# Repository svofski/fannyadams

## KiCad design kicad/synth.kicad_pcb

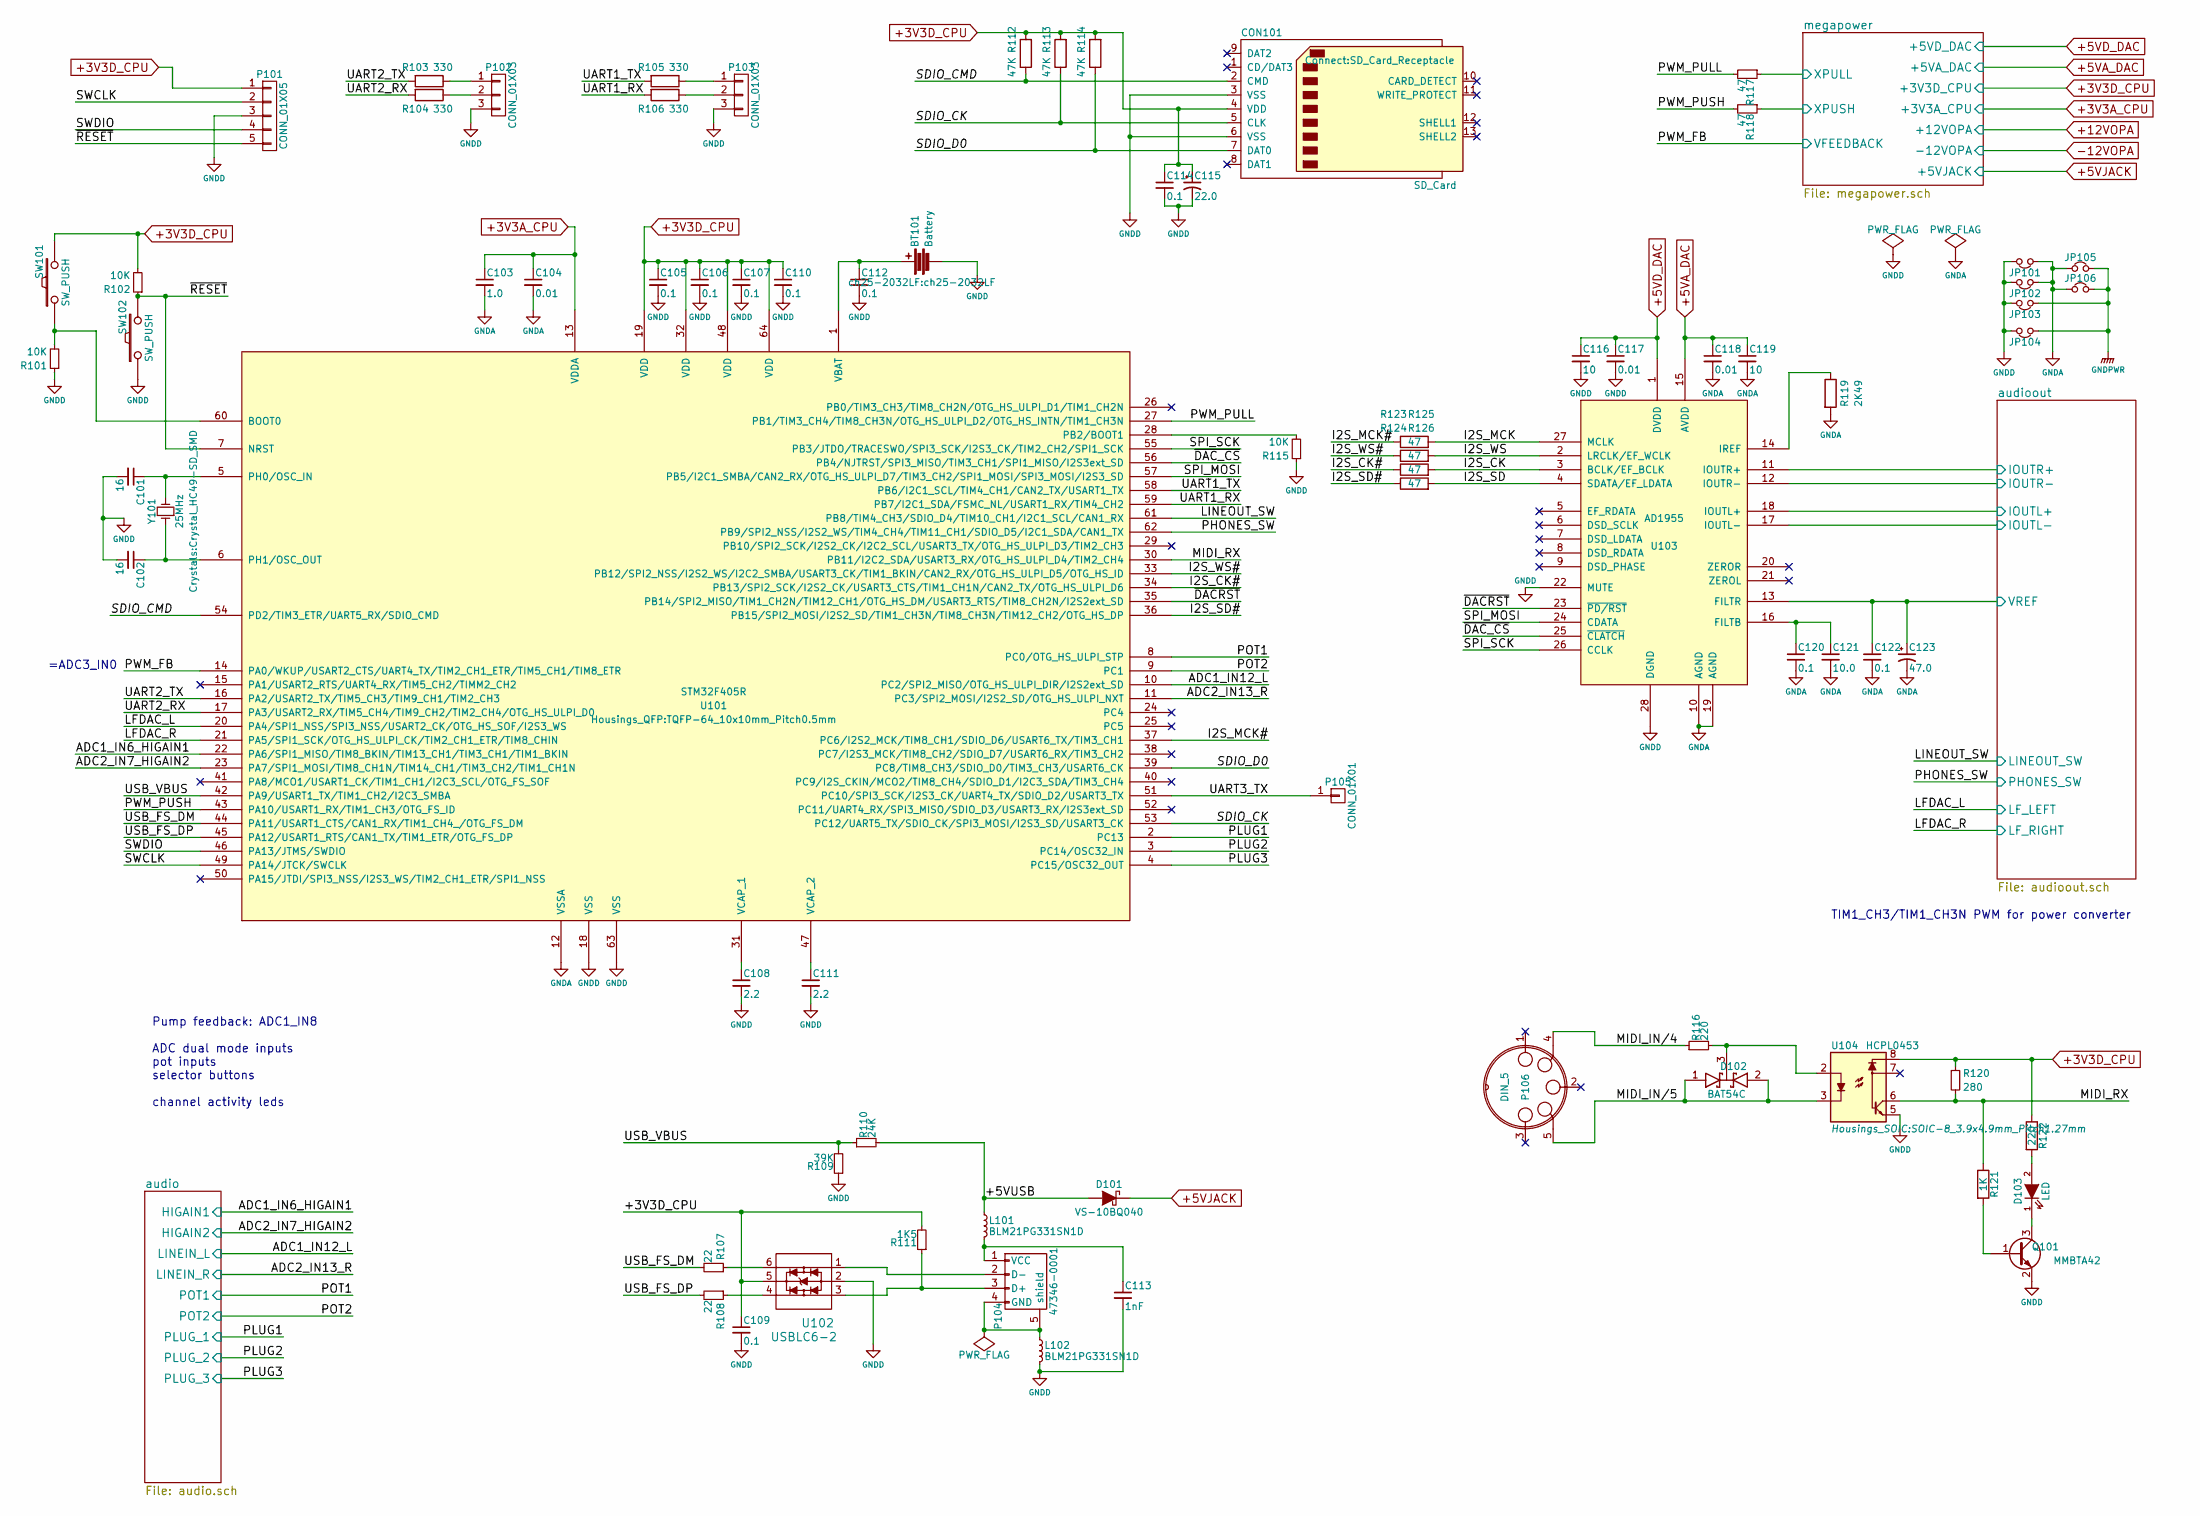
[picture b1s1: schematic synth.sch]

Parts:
BT101: Battery; ch25-2032LF
C101, C102: 16; C_0805
C103: 1.0; C_0805
C104, C117, C118: 0.01; C_0805
C105, C106, C107, C110, C112, C114, C120, C122: 0.1; C_0603
C108, C111: 2.2; C_0805
C109: 0.1; C_0805
C113: 1nF; C_0805
C115: 22.0; TantalC_SizeD_EIA-7343_Reflow
C116, C119: 10; C_0805
C121: 10.0; C_0805
C123: 47.0; c_elec_5x5.3
CON101: SD_Card; SD_Card_Receptacle
D101: VS-10BQ040; SMB_Standard
D102: BAT54C; SOT-23
D103: LED; LED-0805
JP101, JP102, JP103, JP104, JP105, JP106: Jumper_NC_Small; R_0603
L101, L102: BLM21PG331SN1D; R_0805
P101: CONN_01X05; Pin_Header_Straight_1x05
P102, P103: CONN_01X03; Pin_Header_Straight_1x03
P104: 47346-0001; USB_Micro-B
P105: CONN_01X01; 1Pin
P106: DIN_5; din-5
Q101: MMBTA42; SOT-23
R101, R102, R115: 10K; R_0805
R103, R104, R105, R106: 330; R_0805
R107, R108: 22; R_0805
R109: 39K; R_0805
R110: 24K; R_0805
R111: 1K5; R_0805
R112, R113, R114: 47K; R_0805
R116, R122: 220; R_0805
R117, R118, R123, R124, R125, R126: 47; R_0402
R119: 2K49; R_0805
R120: 280; R_0805
R121: 1K; R_0805
SW101, SW102: SW_PUSH; SW_PUSH_SMALL
U101: STM32F405R; TQFP-64_10x10mm_Pitch0.5mm
U102: USBLC6-2; SOT-23-6
U103: AD1955; SSOP-28_5.3x10.2mm_Pitch0.65mm
U104: HCPL0453; SOIC-8_3.9x4.9mm_Pitch1.27mm
Y101: 25MHz; Crystal_HC49-SD_SMD

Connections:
+3V3D_CPU: C105.1, C106.1, C107.1, C109.1, C110.1, C114.1, C115.1, CON101.4 (VDD), P101.1, R102.2, R111.2, R112.2, R113.2, R114.2, R120.1, R122.1, SW101.2, U101.19 (VDD), U101.32 (VDD), U101.48 (VDD), U101.64 (VDD), U102.5, U104.8; also elsewhere on the board
+5VA_DAC: C118.1, C119.1, U103.15 (AVDD); also elsewhere on the board
+5VD_DAC: C116.1, C117.1, U103.1 (DVDD); also elsewhere on the board
+5VJACK: D101.1 (K); also elsewhere on the board
/+5VUSB: D101.2 (A), L101.1, R110.2
/I2S_CK: R125.2, U103.3 (BCLK/EF_BCLK)
/I2S_CK#: R125.1, U101.34 (PB13/SPI2_SCK/I2S2_CK/USART3_CTS/TIM1_C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)
/I2S_MCK: R123.2, U103.27 (MCLK)
/I2S_MCK#: R123.1, U101.37 (PC6/I2S2_MCK/TIM8_CH1/SDIO_D6/USART6_TX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)
/I2S_SD: R126.2, U103.4 (SDATA/EF_LDATA)
/I2S_SD#: R126.1, U101.36 (PB15/SPI2_MOSI/I2S2_SD/TIM1_CH3N/TIM8_C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)
/I2S_WS: R124.2, U103.2 (LRCLK/EF_WCLK)
/I2S_WS#: R124.1, U101.33 (PB12/SPI2_NSS/I2S2_WS/I2C2_SMBA/USART3_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)
/MIDI_IN/4: P106.4, R116.1
/MIDI_IN/5: D102.1 (A), D102.2 (A), P106.5, U104.3
/MIDI_RX: R120.2, R121.1, U101.30 (PB11/I2C2_SDA/USART3_RX/OTG_HS_ULPI_D4/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), U104.6
/PWM_PULL: R117.2, U101.27 (PB1/TIM3_CH4/TIM8_CH3N/OTG_HS_ULPI_D2/O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)
/PWM_PUSH: R118.2, U101.43 (PA10/USART1_RX/TIM1_CH3/OTG_FS_ID)
/SDIO_CK: CON101.5 (CLK), R113.1, U101.53 (PC12/UART5_TX/SDIO_CK/SPI3_MOSI/I2S3_SD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)
/SDIO_CMD: CON101.2 (CMD), R112.1, U101.54 (PD2/TIM3_ETR/UART5_RX/SDIO_CMD)
/SDIO_D0: CON101.7 (DAT0), R114.1, U101.39 (PC8/TIM8_CH3/SDIO_D0/TIM3_CH3/USART6_CK)
/SPI_MOSI: U101.57 (PB5/I2C1_SMBA/CAN2_RX/OTG_HS_ULPI_D7/TI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), U103.24 (CDATA)
/SPI_SCK: U101.55 (PB3/JTDO/TRACESWO/SPI3_SCK/I2S3_CK/TIM2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), U103.26 (CCLK)
/SWCLK: P101.2, U101.49 (PA14/JTCK/SWCLK)
/SWDIO: P101.4, U101.46 (PA13/JTMS/SWDIO)
/UART1_RX: R106.2, U101.59 (PB7/I2C1_SDA/FSMC_NL/USART1_RX/TIM4_CH2)
/UART1_TX: R105.2, U101.58 (PB6/I2C1_SCL/TIM4_CH1/CAN2_TX/USART1_TX)
/UART2_RX: R104.2, U101.17 (PA3/USART2_RX/TIM5_CH4/TIM9_CH2/TIM2_CH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)
/UART2_TX: R103.2, U101.16 (PA2/USART2_TX/TIM5_CH3/TIM9_CH1/TIM2_CH3)
/UART3_TX: P105.1, U101.51 (PC10/SPI3_SCK/I2S3_CK/UART4_TX/SDIO_D2/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)
/USB_FS_DM: R107.2, U101.44 (PA11/USART1_CTS/CAN1_RX/TIM1_CH4_/OTG_F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)
/USB_FS_DP: R108.2, U101.45 (PA12/USART1_RTS/CAN1_TX/TIM1_ETR/OTG_FS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)
/USB_VBUS: R109.2, R110.1, U101.42 (PA9/USART1_TX/TIM1_CH2/I2C3_SMBA)
/audio/HIGAIN1: U101.22 (PA6/SPI1_MISO/TIM8_BKIN/TIM13_CH1/TIM3_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); also elsewhere on the board
/audio/HIGAIN2: U101.23 (PA7/SPI1_MOSI/TIM8_CH1N/TIM14_CH1/TIM3_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); also elsewhere on the board
/audio/LINEIN_L: U101.10 (PC2/SPI2_MISO/OTG_HS_ULPI_DIR/I2S2ext_SD); also elsewhere on the board
/audio/LINEIN_R: U101.11 (PC3/SPI2_MOSI/I2S2_SD/OTG_HS_ULPI_NXT); also elsewhere on the board
/audio/PLUG_1: U101.2 (PC13); also elsewhere on the board
/audio/PLUG_2: U101.3 (PC14/OSC32_IN); also elsewhere on the board
/audio/PLUG_3: U101.4 (PC15/OSC32_OUT); also elsewhere on the board
/audio/POT1: U101.8 (PC0/OTG_HS_ULPI_STP); also elsewhere on the board
/audio/POT2: U101.9 (PC1); also elsewhere on the board
/audioout/IOUTL+: U103.18 (IOUTL+); also elsewhere on the board
/audioout/IOUTL-: U103.17 (IOUTL-); also elsewhere on the board
/audioout/IOUTR+: U103.11 (IOUTR+); also elsewhere on the board
/audioout/IOUTR-: U103.12 (IOUTR-); also elsewhere on the board
/audioout/LF_LEFT: U101.20 (PA4/SPI1_NSS/SPI3_NSS/USART2_CK/OTG_HS_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); also elsewhere on the board
/audioout/LF_RIGHT: U101.21 (PA5/SPI1_SCK/OTG_HS_ULPI_CK/TIM2_CH1_ET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); also elsewhere on the board
/audioout/LINEOUT_SW: U101.61 (PB8/TIM4_CH3/SDIO_D4/TIM10_CH1/I2C1_SCL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); also elsewhere on the board
/audioout/PHONES_SW: U101.62 (PB9/SPI2_NSS/I2S2_WS/TIM4_CH4/TIM11_CH1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); also elsewhere on the board
/audioout/VREF: C122.1, C123.1, U103.13 (FILTR); also elsewhere on the board
/megapower/VFEEDBACK: U101.14 (PA0/WKUP/USART2_CTS/UART4_TX/TIM2_CH1_E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); also elsewhere on the board
/megapower/XPULL: R117.1; also elsewhere on the board
/megapower/XPUSH: R118.1; also elsewhere on the board
/~DACRST: U101.35 (PB14/SPI2_MISO/TIM1_CH2N/TIM12_CH1/OTG_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), U103.23 (~PD/RST)
/~DAC_CS: U101.56 (PB4/NJTRST/SPI3_MISO/TIM3_CH1/SPI1_MISO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), U103.25 (~CLATCH)
/~RESET: P101.5, R102.1, SW102.2, U101.7 (NRST)
GNDA: C103.2, C104.2, C118.2, C119.2, C120.2, C121.2, C122.2, C123.2, JP101.1, JP102.1, JP105.1, JP106.1, R119.2, U101.12 (VSSA), U103.10 (AGND), U103.19 (AGND); also elsewhere on the board
GNDD: BT101.2, C101.2, C102.2, C105.2, C106.2, C107.2, C108.2, C109.2, C110.2, C111.2, C112.2, C113.2, C114.2, C115.2, C116.2, C117.2, CON101.3 (VSS), CON101.6 (VSS), JP101.2, JP102.2, JP103.2, JP104.2, L102.2, P101.3, P102.3, P103.3, Q101.2 (E), R101.1, R109.1, R115.1, SW102.1, U101.18 (VSS), U101.63 (VSS), U102.2, U103.22 (MUTE), U103.28 (DGND), U104.5; also elsewhere on the board
GNDPWR: JP103.1, JP104.1, JP105.2, JP106.2; also elsewhere on the board
unnamed: BT101.1, C112.1, U101.1 (VBAT)
unnamed: C101.1, U101.5 (PH0/OSC_IN), Y101.2
unnamed: C102.1, U101.6 (PH1/OSC_OUT), Y101.1
unnamed: C108.1, U101.31 (VCAP_1)
unnamed: C111.1, U101.47 (VCAP_2)
unnamed: C113.1, L101.2, P104.1 (VCC)
unnamed: C120.1, C121.1, U103.16 (FILTB)
unnamed: D102.3 (K), R116.2, U104.2
unnamed: D103.1 (K), Q101.3 (C)
unnamed: D103.2 (A), R122.2
unnamed: L102.1, P104.4 (GND), P104.5 (shield)
unnamed: P102.1, R103.1
unnamed: P102.2, R104.1
unnamed: P103.1, R105.1
unnamed: P103.2, R106.1
unnamed: P104.2 (D-), U102.1
unnamed: P104.3 (D+), R111.1, U102.3
unnamed: Q101.1 (B), R121.2
unnamed: R101.2, SW101.1, U101.60 (BOOT0)
unnamed: R107.1, U102.6
unnamed: R108.1, U102.4
unnamed: R115.2, U101.28 (PB2/BOOT1)
unnamed: R119.1, U103.14 (IREF)

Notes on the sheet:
TIM1_CH3/TIM1_CH3N PWM for power converter
Pump feedback: ADC1_IN8 ADC dual mode inputs pot inputs selector buttons channel activity leds
=ADC3_IN0

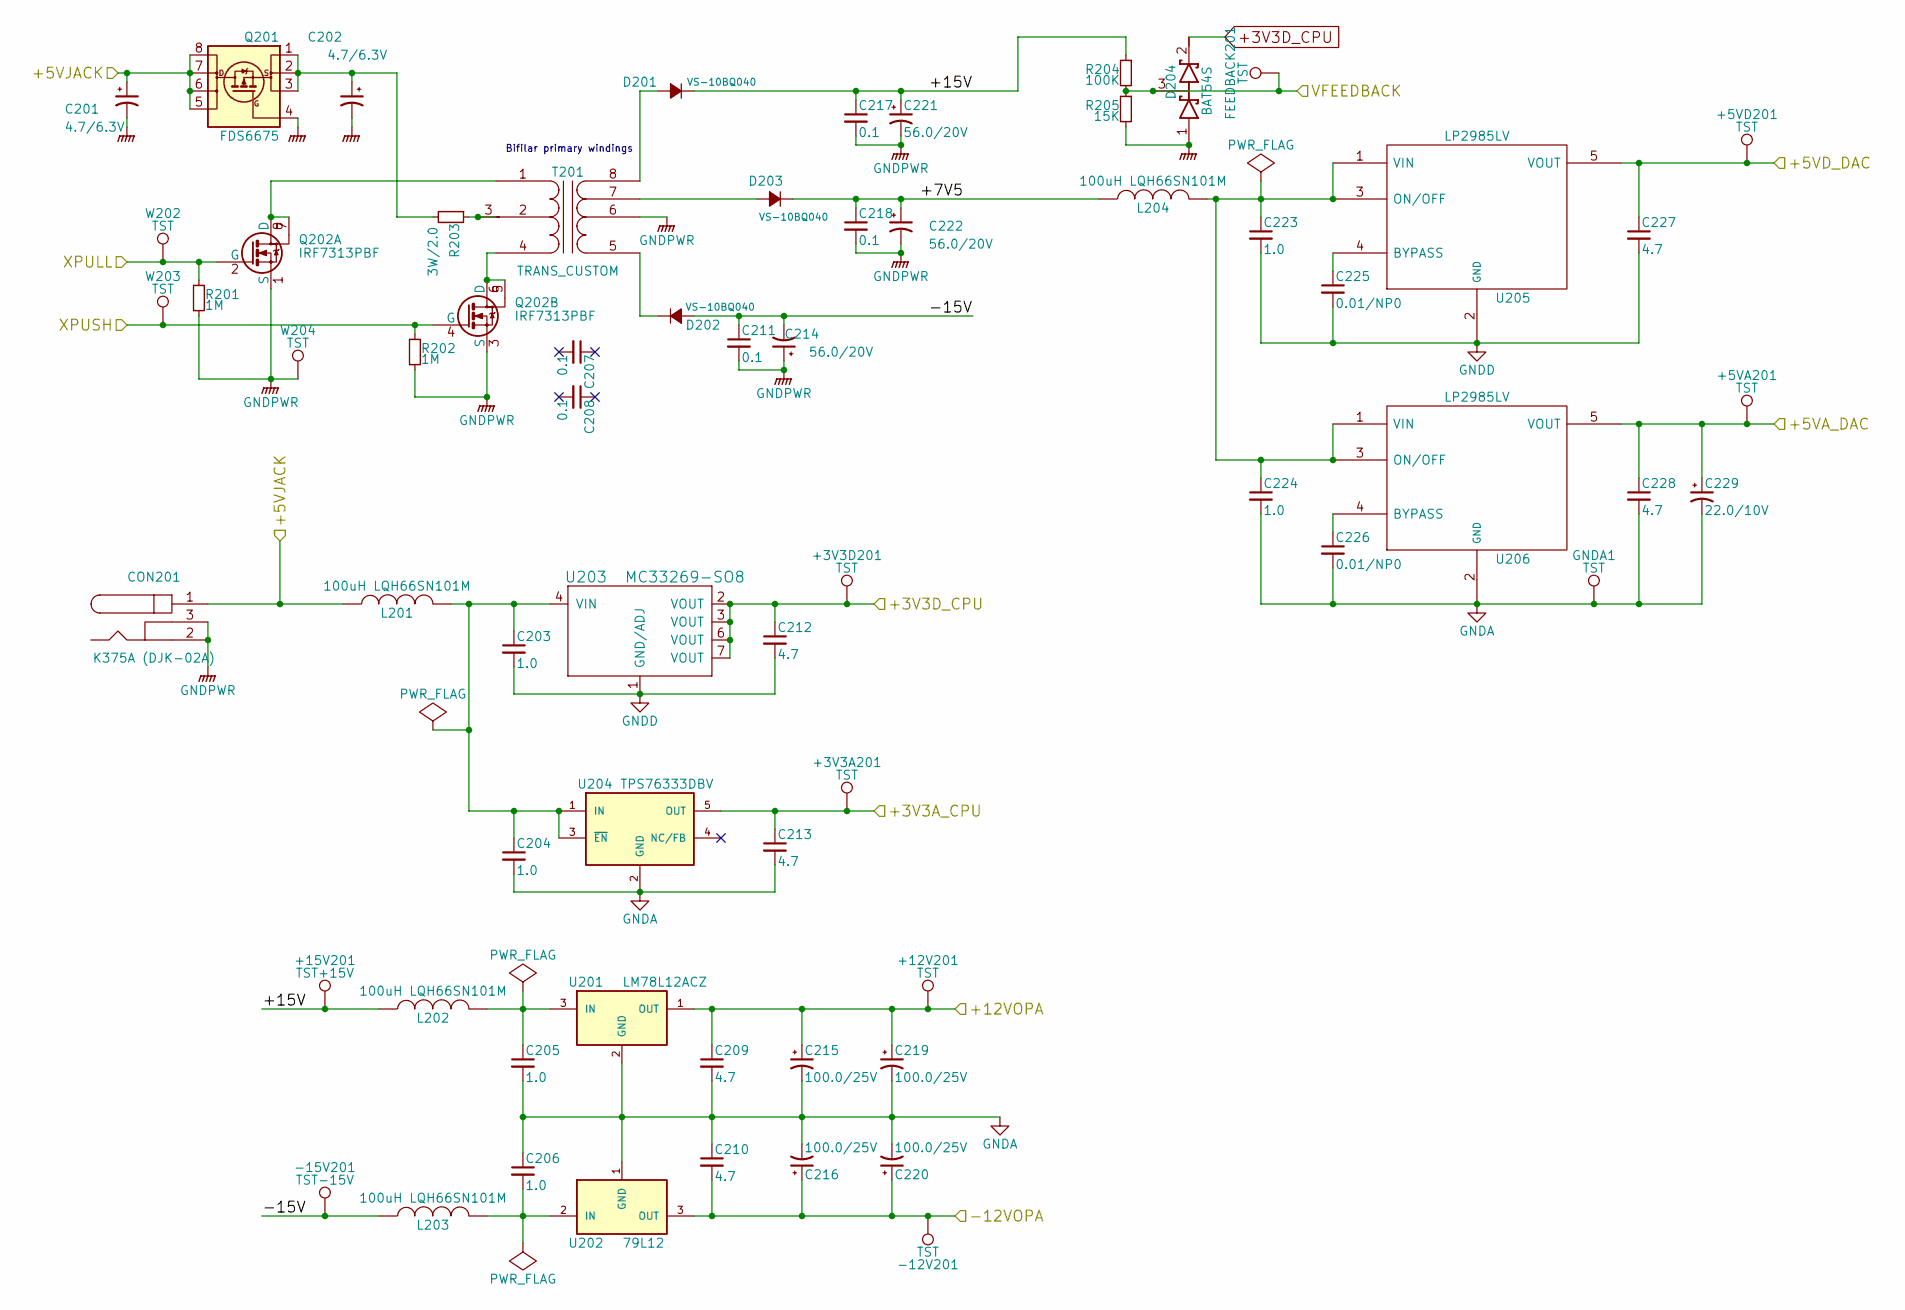
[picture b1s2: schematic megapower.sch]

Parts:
+3V3A201, +3V3D201, +5VA201, +5VD201, +12V201: TST; PINTST
+15V201: TST+15V; PINTST
-12V201: TST; PINTST
-15V201: TST-15V; PINTST
C201, C202: 4.7/6.3V; c_elec_5x5.3
C203, C204, C205, C206, C223, C224: 1.0; C_0805
C207, C208, C211: 0.1; C_0805
C209, C210, C212, C213, C227, C228: 4.7; C_0805
C214, C221, C222: 56.0/20V; C_Radial_D6.3_L11.2_P2.5
C215, C216, C219, C220: 100.0/25V; c_elec_6.3x7.7
C217, C218: 0.1; C_0603
C225, C226: 0.01/NP0; C_0805
C229: 22.0/10V; TantalC_SizeC_EIA-6032_Reflow
CON201: K375A (DJK-02A); BARREL_JACK
D201, D202, D203: VS-10BQ040; SMB_Standard
D204: BAT54S; SOT-23
FEEDBACK201: TST; PINTST
GNDA1: TST; PINTST
L201, L202, L203, L204: 100uH LQH66SN101M; Choke_SMD_6.3x6.3_H3
Q201: FDS6675; SOIC-8_3.9x4.9mm_Pitch1.27mm
Q202: IRF7313PBF; SO-8
R201, R202: 1M; R_0805
R203: 3W/2.0; R_0805
R204: 100K; R_0805
R205: 15K; R_0805
T201: TRANS_CUSTOM; Coilcraft-Q4434-B_Rhombus-T1311
U201: LM78L12ACZ; TO-92_Inline_Wide
U202: 79L12; TO-92_Inline_Wide
U203: MC33269-SO8; SOIC-8_3.9x4.9mm_Pitch1.27mm
U204: TPS76333DBV; SOT-23-5
U205, U206: LP2985LV; SOT-23-5
W202, W203, W204: TST; PINTST

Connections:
+3V3D_CPU: +3V3D201.1, C212.1, D204.2 (K), U203.2 (VOUT), U203.3 (VOUT), U203.6 (VOUT), U203.7 (VOUT); also elsewhere on the board
+5VA_DAC: +5VA201.1, C228.1, C229.1, U206.5 (VOUT); also elsewhere on the board
+5VD_DAC: +5VD201.1, C227.1, U205.5 (VOUT); also elsewhere on the board
+5VJACK: C201.1, CON201.1, L201.1, Q201.5 (D), Q201.6 (D), Q201.7 (D), Q201.8 (D); also elsewhere on the board
+12VOPA: +12V201.1, C209.1, C215.1, C219.1, U201.1 (OUT); also elsewhere on the board
-12VOPA: -12V201.1, C210.2, C216.1, C220.1, U202.3 (OUT); also elsewhere on the board
/megapower/+7V5: C218.1, C222.1, D203.1 (K), L204.1
/megapower/+15V: +15V201.1, C217.1, C221.1, D201.1 (K), L202.1, R204.1
/megapower/-15V: -15V201.1, C211.1, C214.2, D202.2 (A), L203.1
/megapower/VFEEDBACK: D204.3 (common), FEEDBACK201.1, R204.2, R205.1; also elsewhere on the board
/megapower/XPULL: Q202.2 (G), R201.1, W202.1; also elsewhere on the board
/megapower/XPUSH: Q202.4 (G), R202.1, W203.1; also elsewhere on the board
GNDA: C204.2, C205.2, C206.1, C209.2, C210.1, C213.2, C215.2, C216.2, C219.2, C220.2, C224.2, C226.2, C228.2, C229.2, GNDA1.1, U201.2 (GND), U202.1 (GND), U204.2 (GND), U206.2 (GND); also elsewhere on the board
GNDD: C203.2, C212.2, C223.2, C225.2, C227.2, U203.1 (GND/ADJ), U205.2 (GND); also elsewhere on the board
GNDPWR: C201.2, C202.2, C211.2, C214.1, C217.2, C218.2, C221.2, C222.2, CON201.2, CON201.3, D204.1 (A), Q201.4 (G), Q202.1 (S), Q202.3 (S), R201.2, R202.2, R205.2, T201.6, W204.1; also elsewhere on the board
unnamed: C202.1, Q201.1 (S), Q201.2 (S), Q201.3 (S), R203.2
unnamed: C203.1, C204.1, L201.2, U203.4 (VIN), U204.1 (IN), U204.3 (~EN~)
unnamed: C205.1, L202.2, U201.3 (IN)
unnamed: C206.2, L203.2, U202.2 (IN)
unnamed: C223.1, C224.1, L204.2, U205.1 (VIN), U205.3 (ON/OFF), U206.1 (VIN), U206.3 (ON/OFF)
unnamed: C225.1, U205.4 (BYPASS)
unnamed: C226.1, U206.4 (BYPASS)
unnamed: D201.2 (A), T201.8 (S2)
unnamed: D202.1 (K), T201.5 (S1)
unnamed: D203.2 (A), T201.7
unnamed: Q202.5, Q202.6 (D), T201.4 (PR2)
unnamed: Q202.7, Q202.8 (D), T201.1 (PR1)
unnamed: R203.1, T201.2 (PM), T201.3

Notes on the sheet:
Bifilar primary windings

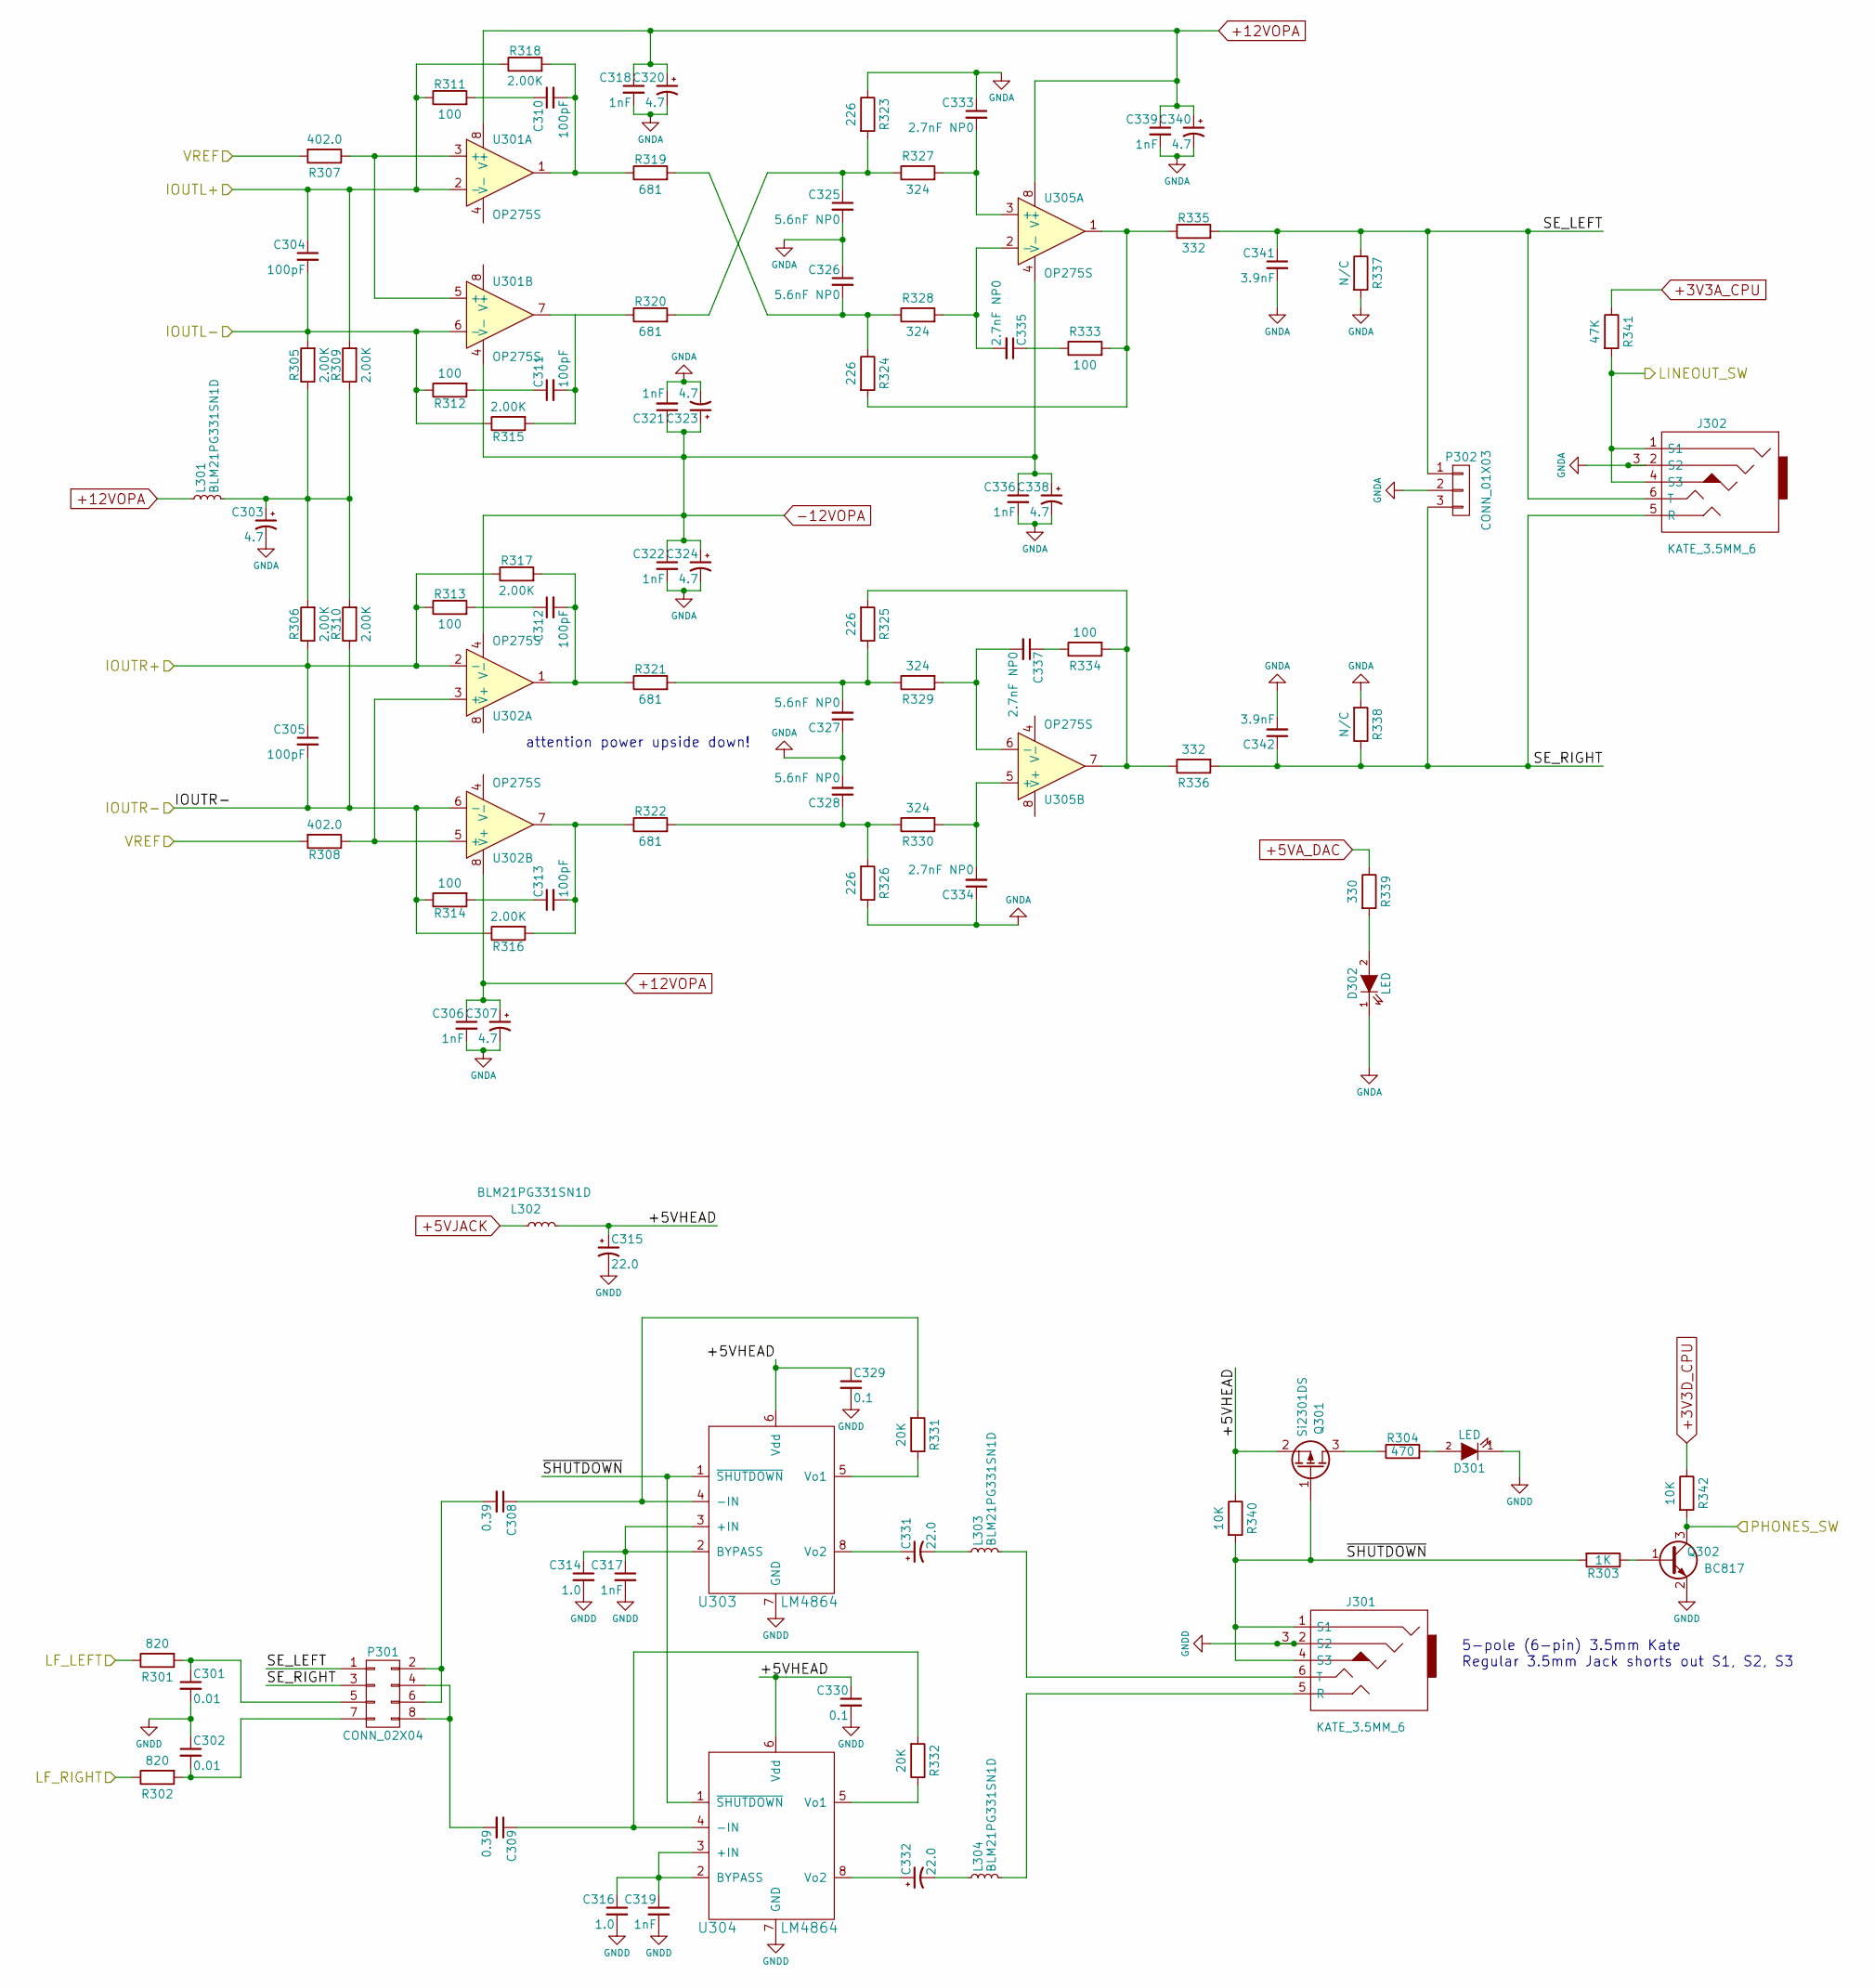
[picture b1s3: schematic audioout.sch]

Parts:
C301, C302: 0.01; C_0805
C303, C307, C320, C323, C324, C338, C340: 4.7; C_0805
C304, C305, C310, C311, C312, C313: 100pF; C_0805
C306, C317, C318, C319, C321, C322, C336, C339: 1nF; C_0805
C308, C309: 0.39; C_0805
C314, C316: 1.0; C_0805
C315, C331, C332: 22.0; TantalC_SizeC_EIA-6032_Reflow
C325, C326, C327, C328: 5.6nF NP0; C_0805
C329, C330: 0.1; C_0805
C333, C334, C335, C337: 2.7nF NP0; C_0805
C341, C342: 3.9nF; C_0805
D301, D302: LED; LED-0805
J301, J302: KATE_3.5MM_6; JACK_35MM_KATE_6
L301, L302, L303, L304: BLM21PG331SN1D; R_0805
P301: CONN_02X04; Pin_Header_Straight_2x04
P302: CONN_01X03; Pin_Header_Straight_1x03
Q301: Si2301DS; SOT-23
Q302: BC817; SOT-23
R301, R302: 820; R_1206
R303: 1K; R_0805
R304: 470; R_0805
R305, R306, R309, R310, R315, R316, R317, R318: 2.00K; R_0805
R307, R308: 402.0; R_1206
R311, R312, R313, R314, R333, R334: 100; R_0805
R319, R320, R321, R322: 681; R_0805
R323, R324, R325, R326: 226; R_0805
R327, R328, R329, R330: 324; R_0805
R331, R332: 20K; R_0805
R335, R336: 332; R_0805
R337, R338: N/C; R_0805
R339: 330; R_0805
R340, R342: 10K; R_0805
R341: 47K; R_0805
U301, U302, U305: OP275S; SOIC-8_3.9x4.9mm_Pitch1.27mm
U303, U304: LM4864; SOIC-8_3.9x4.9mm_Pitch1.27mm

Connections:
+3V3D_CPU: R342.1; also elsewhere on the board
+5VA_DAC: R339.1; also elsewhere on the board
+5VJACK: L302.1; also elsewhere on the board
+12VOPA: C306.1, C307.1, C318.1, C320.1, C339.1, C340.1, L301.1, U301.8 (V+), U302.8 (V+), U305.8 (V+); also elsewhere on the board
-12VOPA: C321.1, C322.1, C323.1, C324.1, C336.1, C338.1, U301.4 (V-), U302.4 (V-), U305.4 (V-); also elsewhere on the board
/audioout/+5VHEAD: C315.1, C329.1, C330.1, L302.2, Q301.2 (S), R340.1, U303.6 (Vdd), U304.6 (Vdd)
/audioout/IOUTL+: C304.1, R309.2, R311.1, R318.1, U301.2 (-); also elsewhere on the board
/audioout/IOUTL-: C304.2, R305.2, R312.1, R315.1, U301.6 (-); also elsewhere on the board
/audioout/IOUTR+: C305.1, R306.1, R313.1, R317.1, U302.2 (-); also elsewhere on the board
/audioout/IOUTR-: C305.2, R310.1, R314.1, R316.1, U302.6 (-); also elsewhere on the board
/audioout/LF_LEFT: R301.1; also elsewhere on the board
/audioout/LF_RIGHT: R302.1; also elsewhere on the board
/audioout/LINEOUT_SW: J302.1 (S1), J302.4 (S3), R341.2; also elsewhere on the board
/audioout/PHONES_SW: Q302.3 (C), R342.2; also elsewhere on the board
/audioout/SE_LEFT: C341.1, J302.6 (T), P301.1, P302.1, R335.2, R337.1
/audioout/SE_RIGHT: C342.1, J302.5 (R), P301.3, P302.3, R336.2, R338.1
/audioout/VREF: R307.2, R308.2; also elsewhere on the board
/audioout/~SHUTDOWN: J301.1 (S1), J301.4 (S3), Q301.1 (G), R303.2, R340.2, U303.1 (~SHUTDOWN), U304.1 (~SHUTDOWN)
GNDA: C303.2, C306.2, C307.2, C318.2, C320.2, C321.2, C322.2, C323.2, C324.2, C325.2, C326.1, C327.1, C328.2, C333.1, C334.1, C336.2, C338.2, C339.2, C340.2, C341.2, C342.2, D302.1 (K), J302.2 (S2), J302.3, P302.2, R323.1, R326.1, R337.2, R338.2; also elsewhere on the board
GNDD: C301.2, C302.1, C314.2, C315.2, C316.2, C317.2, C319.2, C329.2, C330.2, D301.1 (K), J301.2 (S2), J301.3, Q302.2 (E), U303.7 (GND), U304.7 (GND); also elsewhere on the board
unnamed: C301.1, P301.5, R301.2
unnamed: C302.2, P301.7, R302.2
unnamed: C303.1, L301.2, R305.1, R306.2, R309.1, R310.2
unnamed: C308.2, P301.2, P301.6
unnamed: C309.2, P301.4, P301.8
unnamed: C310.1, R311.2
unnamed: C310.2, R318.2, R319.1, U301.1
unnamed: C311.1, R312.2
unnamed: C312.1, R313.2
unnamed: C312.2, R317.2, R321.1, U302.1
unnamed: C313.1, R314.2
unnamed: C313.2, R316.2, R322.1, U302.7
unnamed: C314.1, C317.1, U303.2 (BYPASS), U303.3 (+IN)
unnamed: C316.1, C319.1, U304.2 (BYPASS), U304.3 (+IN)
unnamed: C325.1, R320.2, R323.2, R327.1
unnamed: C326.2, R319.2, R324.1, R328.1
unnamed: C327.2, R321.2, R325.1, R329.1
unnamed: C328.1, R322.2, R326.2, R330.1
unnamed: C331.1, U303.8 (Vo2)
unnamed: C331.2, L303.1
unnamed: C332.1, U304.8 (Vo2)
unnamed: C332.2, L304.1
unnamed: C333.2, R327.2, U305.3 (+)
unnamed: C334.2, R330.2, U305.5 (+)
unnamed: C335.1, R333.1
unnamed: C335.2, R328.2, U305.2 (-)
unnamed: C337.1, R334.1
unnamed: C337.2, R329.2, U305.6 (-)
unnamed: D301.2 (A), R304.2
unnamed: D302.2 (A), R339.2
unnamed: J301.5 (R), L304.2
unnamed: J301.6 (T), L303.2
unnamed: Q301.3 (D), R304.1
unnamed: Q302.1 (B), R303.1
unnamed: R307.1, U301.3 (+), U301.5 (+)
unnamed: R308.1, U302.3 (+), U302.5 (+)
unnamed: R324.2, R333.2, R335.1, U305.1
unnamed: R325.2, R334.2, R336.1, U305.7
unnamed: R331.1, U303.5 (Vo1)
unnamed: R332.1, U304.5 (Vo1)

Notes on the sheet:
attention power upside down!
5-pole (6-pin) 3.5mm Kate Regular 3.5mm Jack shorts out S1, S2, S3

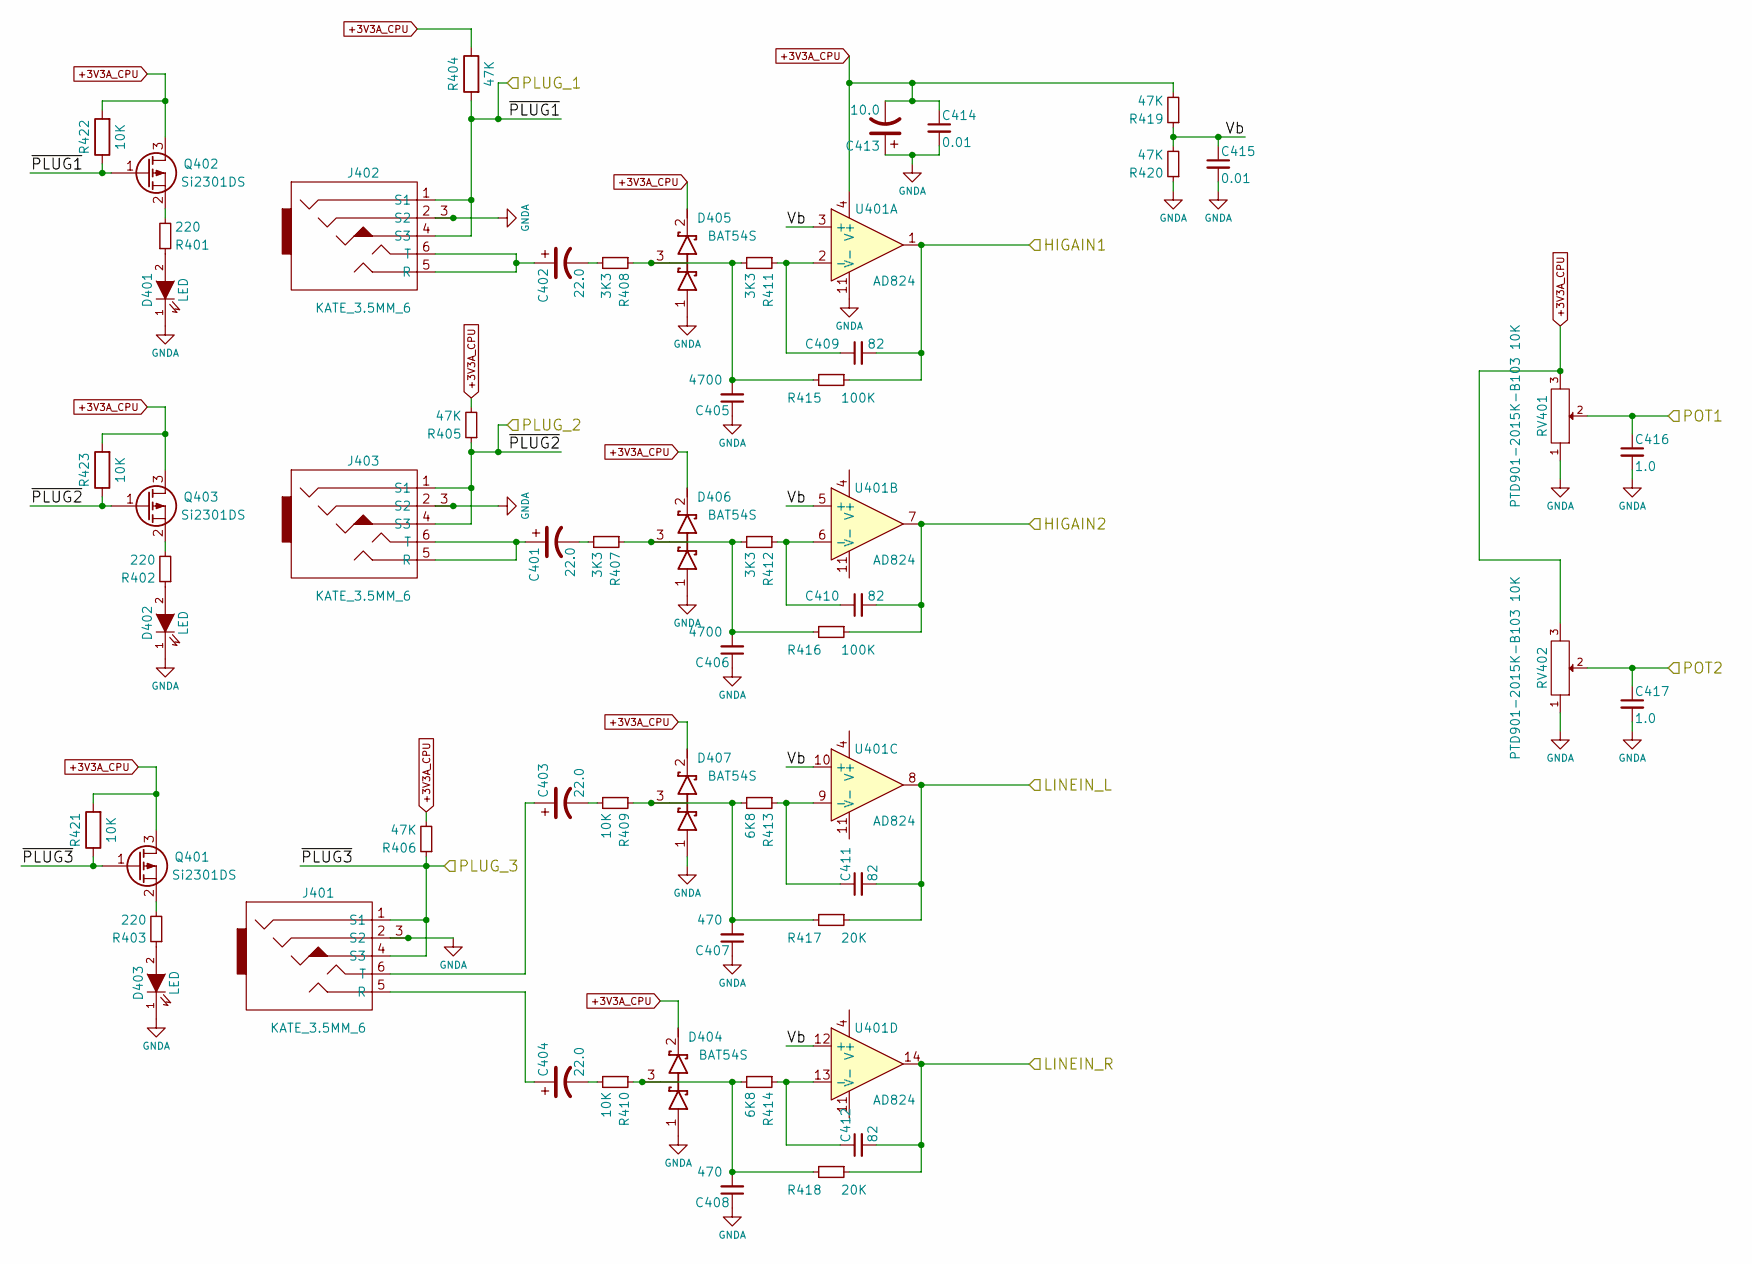
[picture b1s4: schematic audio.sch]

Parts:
C401, C402, C403, C404: 22.0; TantalC_SizeC_EIA-6032_Reflow
C405, C406: 4700; C_0805
C407, C408: 470; C_0805
C409, C410, C411, C412: 82; C_0805
C413: 10.0; C_0805
C414, C415: 0.01; C_0805
C416, C417: 1.0; C_0805
D401, D402, D403: LED; LED-0805
D404, D405, D406, D407: BAT54S; SOT-23
J401, J402, J403: KATE_3.5MM_6; JACK_35MM_KATE_6
Q401, Q402, Q403: Si2301DS; SOT-23
R401, R402, R403: 220; R_0805
R404, R405, R406, R419, R420: 47K; R_0805
R407, R408, R411, R412: 3K3; R_0805
R409, R410, R421, R422, R423: 10K; R_0805
R413, R414: 6K8; R_0805
R415, R416: 100K; R_0805
R417, R418: 20K; R_0805
RV401, RV402: PTD901-2015K-B103 10K; Potentiometer_Alps-RK16-single_largePads
U401: AD824; SOIC-14_3.9x8.7mm_Pitch1.27mm

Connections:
/audio/HIGAIN1: C409.2, R415.1, U401.1; also elsewhere on the board
/audio/HIGAIN2: C410.2, R416.1, U401.7; also elsewhere on the board
/audio/LINEIN_L: C411.2, R417.1, U401.8; also elsewhere on the board
/audio/LINEIN_R: C412.2, R418.1, U401.14; also elsewhere on the board
/audio/PLUG_1: J402.1 (S1), J402.4 (S3), Q402.1 (G), R404.2, R422.1; also elsewhere on the board
/audio/PLUG_2: J403.1 (S1), J403.4 (S3), Q403.1 (G), R405.1, R423.1; also elsewhere on the board
/audio/PLUG_3: J401.1 (S1), J401.4 (S3), Q401.1 (G), R406.1, R421.1; also elsewhere on the board
/audio/POT1: C416.1, RV401.2; also elsewhere on the board
/audio/POT2: C417.1, RV402.2; also elsewhere on the board
/audio/Vb: C415.1, R419.1, R420.2, U401.3 (+), U401.5 (+), U401.10 (+), U401.12 (+)
GNDA: C405.1, C406.1, C407.1, C408.1, C413.1, C414.2, C415.2, C416.2, C417.2, D401.1 (K), D402.1 (K), D403.1 (K), D404.1 (A), D405.1 (A), D406.1 (A), D407.1 (A), J401.2 (S2), J401.3, J402.2 (S2), J402.3, J403.2 (S2), J403.3, R420.1, RV401.1, RV402.1, U401.11 (V-); also elsewhere on the board
unnamed: C401.1, J403.5 (R), J403.6 (T)
unnamed: C401.2, R407.2
unnamed: C402.1, J402.5 (R), J402.6 (T)
unnamed: C402.2, R408.2
unnamed: C403.1, J401.6 (T)
unnamed: C403.2, R409.2
unnamed: C404.1, J401.5 (R)
unnamed: C404.2, R410.2
unnamed: C405.2, D405.3 (common), R408.1, R411.2, R415.2
unnamed: C406.2, D406.3 (common), R407.1, R412.2, R416.2
unnamed: C407.2, D407.3 (common), R409.1, R413.2, R417.2
unnamed: C408.2, D404.3 (common), R410.1, R414.2, R418.2
unnamed: C409.1, R411.1, U401.2 (-)
unnamed: C410.1, R412.1, U401.6 (-)
unnamed: C411.1, R413.1, U401.9 (-)
unnamed: C412.1, R414.1, U401.13 (-)
unnamed: D401.2 (A), R401.1
unnamed: D402.2 (A), R402.1
unnamed: D403.2 (A), R403.1

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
